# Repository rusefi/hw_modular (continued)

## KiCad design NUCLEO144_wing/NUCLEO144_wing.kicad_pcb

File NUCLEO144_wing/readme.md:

https://rusefi.com/forum/viewtopic.php?f=4&t=1522

Rev 0.1 send to fab 02/25/2019

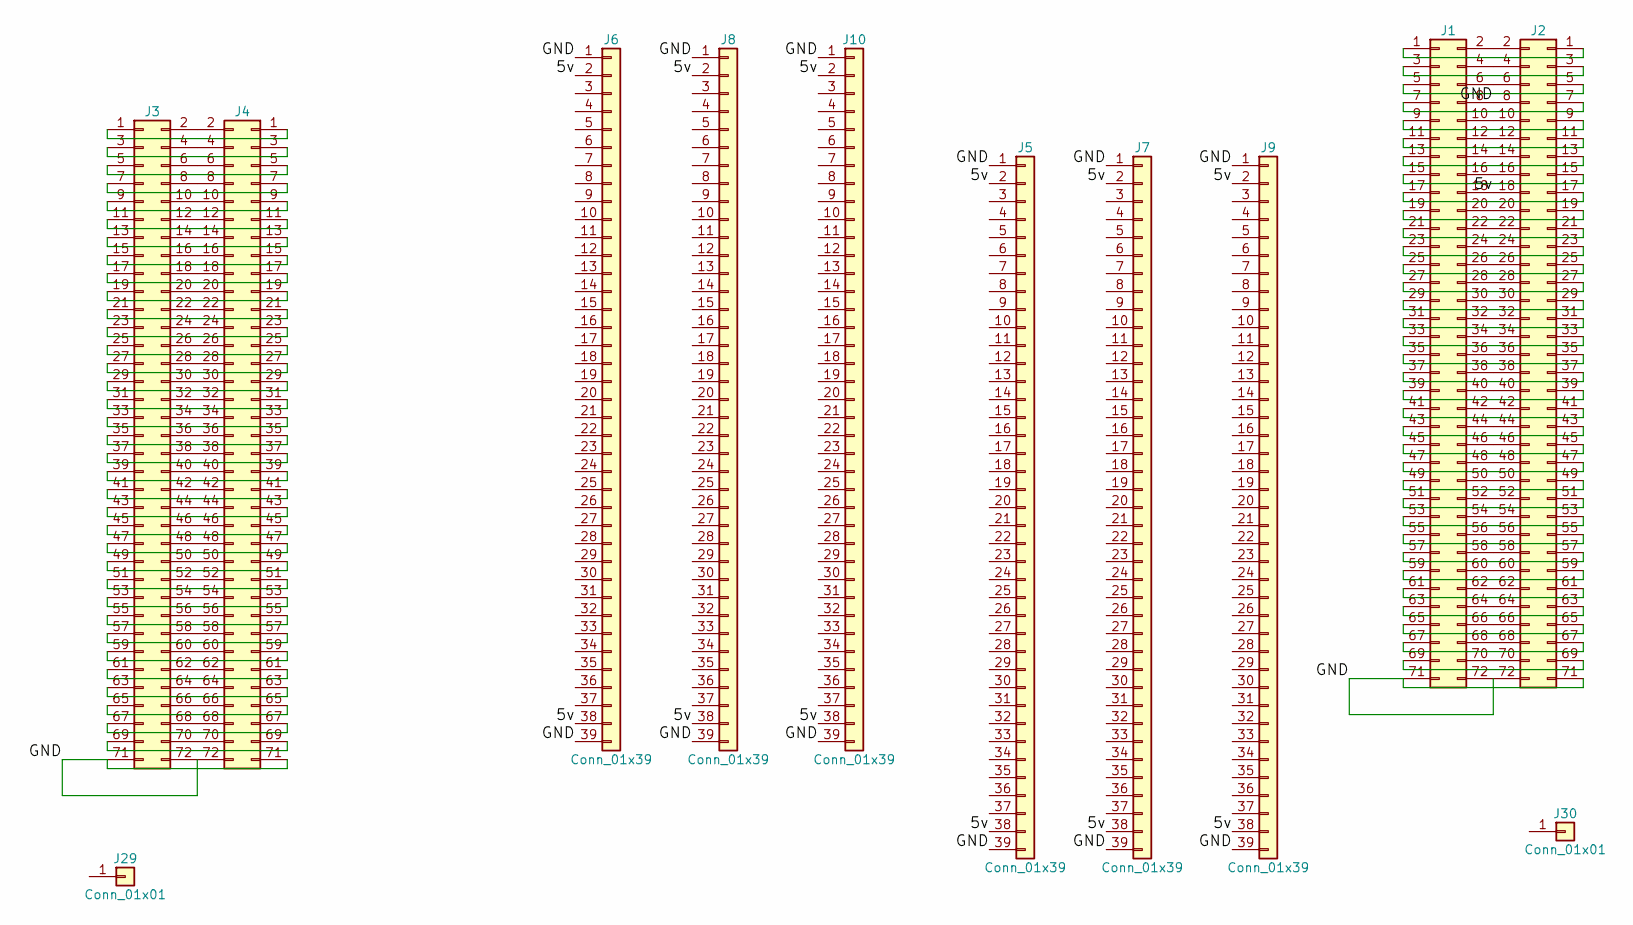
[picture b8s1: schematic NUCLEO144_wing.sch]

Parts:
J1, J2, J3, J4: Conn_02x36_Top_Bottom; Pin_Header_Straight_2x36_Pitch2.54mm
J5, J6, J7, J8, J9, J10: Conn_01x39; rusEfi_4x39_Pitch2.54mm
J29, J30: Conn_01x01; 1pin

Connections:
/5v: J1.18, J2.18, J5.2, J5.38, J6.2, J6.38, J7.2, J7.38, J8.2, J8.38, J9.2, J9.38, J10.2, J10.38
/GND: J1.8, J1.71, J1.72, J2.8, J2.71, J2.72, J3.71, J3.72, J4.71, J4.72, J5.1, J5.39, J6.1, J6.39, J7.1, J7.39, J8.1, J8.39, J9.1, J9.39, J10.1, J10.39
unnamed: J1.1, J2.1
unnamed: J1.2, J2.2
unnamed: J1.3, J2.3
unnamed: J1.4, J2.4
unnamed: J1.5, J2.5
unnamed: J1.6, J2.6
unnamed: J1.7, J2.7
unnamed: J1.9, J2.9
unnamed: J1.10, J2.10
unnamed: J1.11, J2.11
unnamed: J1.12, J2.12
unnamed: J1.13, J2.13
unnamed: J1.14, J2.14
unnamed: J1.15, J2.15
unnamed: J1.16, J2.16
unnamed: J1.17, J2.17
unnamed: J1.19, J2.19
unnamed: J1.20, J2.20
unnamed: J1.21, J2.21
unnamed: J1.22, J2.22
unnamed: J1.23, J2.23
unnamed: J1.24, J2.24
unnamed: J1.25, J2.25
unnamed: J1.26, J2.26
unnamed: J1.27, J2.27
unnamed: J1.28, J2.28
unnamed: J1.29, J2.29
unnamed: J1.30, J2.30
unnamed: J1.31, J2.31
unnamed: J1.32, J2.32
unnamed: J1.33, J2.33
unnamed: J1.34, J2.34
unnamed: J1.35, J2.35
unnamed: J1.36, J2.36
unnamed: J1.37, J2.37
unnamed: J1.38, J2.38
unnamed: J1.39, J2.39
unnamed: J1.40, J2.40
unnamed: J1.41, J2.41
unnamed: J1.42, J2.42
unnamed: J1.43, J2.43
unnamed: J1.44, J2.44
unnamed: J1.45, J2.45
unnamed: J1.46, J2.46
unnamed: J1.47, J2.47
unnamed: J1.48, J2.48
unnamed: J1.49, J2.49
unnamed: J1.50, J2.50
unnamed: J1.51, J2.51
unnamed: J1.52, J2.52
unnamed: J1.53, J2.53
unnamed: J1.54, J2.54
unnamed: J1.55, J2.55
unnamed: J1.56, J2.56
unnamed: J1.57, J2.57
unnamed: J1.58, J2.58
unnamed: J1.59, J2.59
unnamed: J1.60, J2.60
unnamed: J1.61, J2.61
unnamed: J1.62, J2.62
unnamed: J1.63, J2.63
unnamed: J1.64, J2.64
unnamed: J1.65, J2.65
unnamed: J1.66, J2.66
unnamed: J1.67, J2.67
unnamed: J1.68, J2.68
unnamed: J1.69, J2.69
unnamed: J1.70, J2.70
unnamed: J3.1, J4.1
unnamed: J3.2, J4.2
unnamed: J3.3, J4.3
unnamed: J3.4, J4.4
unnamed: J3.5, J4.5
unnamed: J3.6, J4.6
unnamed: J3.7, J4.7
unnamed: J3.8, J4.8
unnamed: J3.9, J4.9
unnamed: J3.10, J4.10
unnamed: J3.11, J4.11
unnamed: J3.12, J4.12
unnamed: J3.13, J4.13
unnamed: J3.14, J4.14
unnamed: J3.15, J4.15
unnamed: J3.16, J4.16
unnamed: J3.17, J4.17
unnamed: J3.18, J4.18
unnamed: J3.19, J4.19
unnamed: J3.20, J4.20
unnamed: J3.21, J4.21
unnamed: J3.22, J4.22
unnamed: J3.23, J4.23
unnamed: J3.24, J4.24
unnamed: J3.25, J4.25
unnamed: J3.26, J4.26
unnamed: J3.27, J4.27
unnamed: J3.28, J4.28
unnamed: J3.29, J4.29
unnamed: J3.30, J4.30
unnamed: J3.31, J4.31
unnamed: J3.32, J4.32
unnamed: J3.33, J4.33
unnamed: J3.34, J4.34
unnamed: J3.35, J4.35
unnamed: J3.36, J4.36
unnamed: J3.37, J4.37
unnamed: J3.38, J4.38
unnamed: J3.39, J4.39
unnamed: J3.40, J4.40
unnamed: J3.41, J4.41
unnamed: J3.42, J4.42
unnamed: J3.43, J4.43
unnamed: J3.44, J4.44
unnamed: J3.45, J4.45
unnamed: J3.46, J4.46
unnamed: J3.47, J4.47
unnamed: J3.48, J4.48
unnamed: J3.49, J4.49
unnamed: J3.50, J4.50
unnamed: J3.51, J4.51
unnamed: J3.52, J4.52
unnamed: J3.53, J4.53
unnamed: J3.54, J4.54
unnamed: J3.55, J4.55
unnamed: J3.56, J4.56
unnamed: J3.57, J4.57
unnamed: J3.58, J4.58
unnamed: J3.59, J4.59
unnamed: J3.60, J4.60
unnamed: J3.61, J4.61
unnamed: J3.62, J4.62
unnamed: J3.63, J4.63
unnamed: J3.64, J4.64
unnamed: J3.65, J4.65
unnamed: J3.66, J4.66
unnamed: J3.67, J4.67
unnamed: J3.68, J4.68
unnamed: J3.69, J4.69
unnamed: J3.70, J4.70

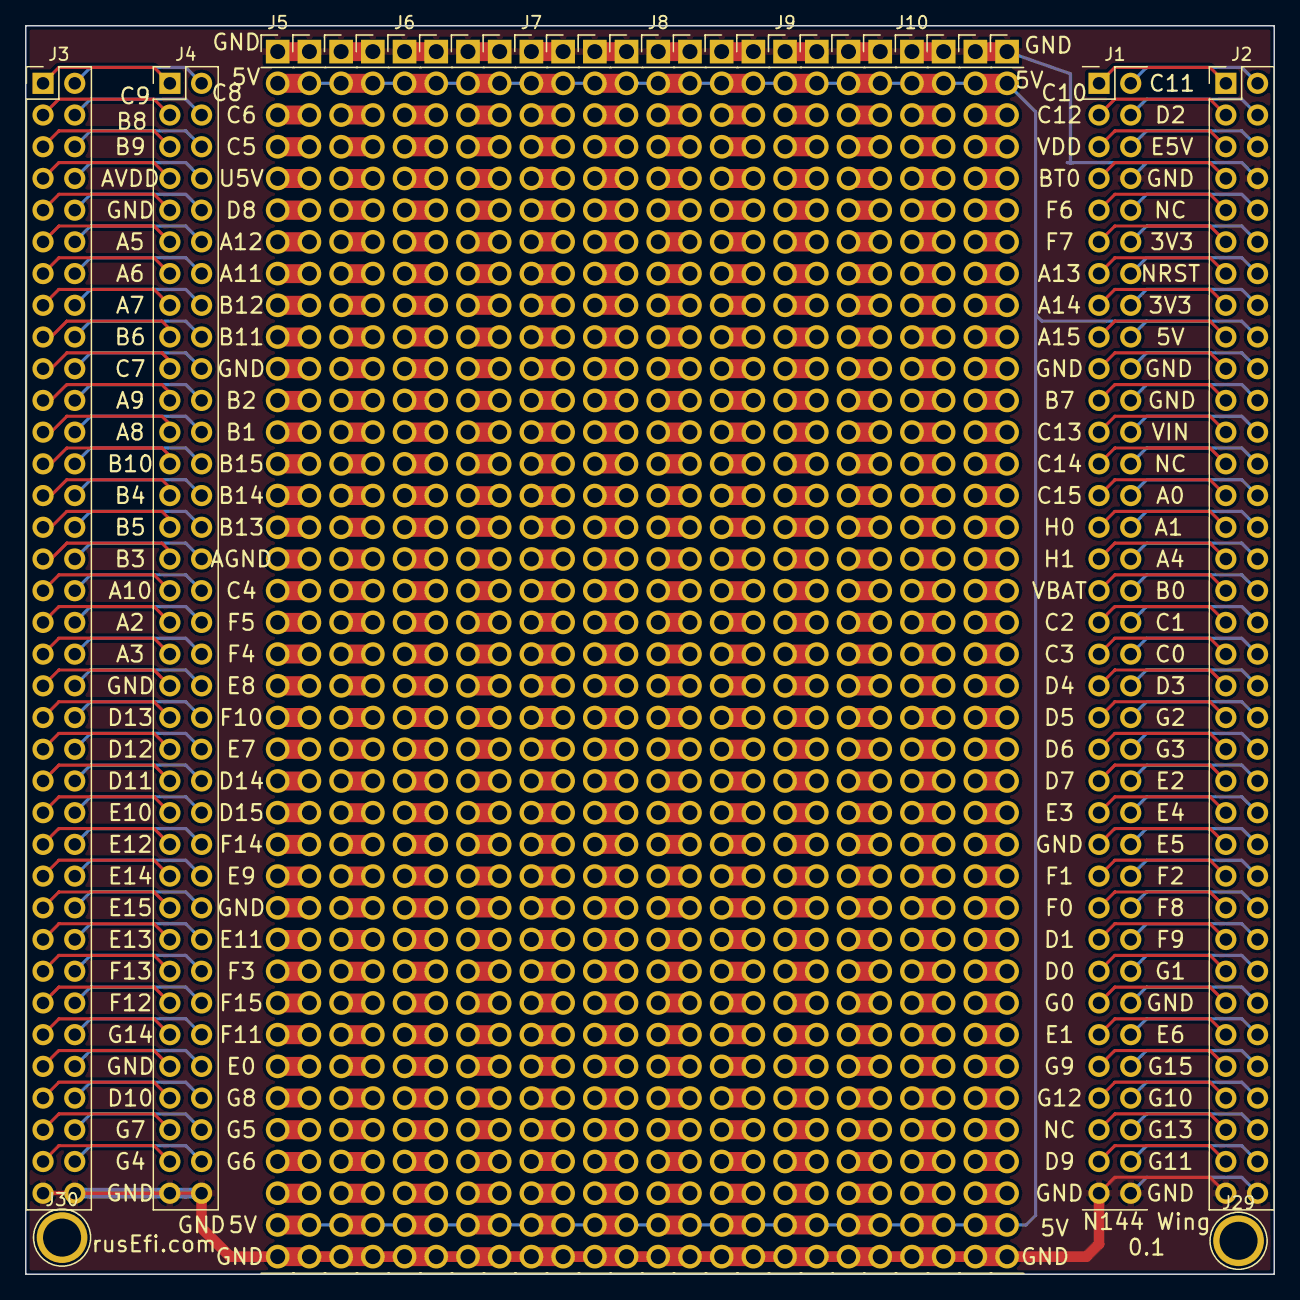
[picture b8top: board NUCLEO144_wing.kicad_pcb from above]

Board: 2 copper layers, 100.0 x 100.0 mm, 12 parts (0 on the bottom side), 140 nets.

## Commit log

2019-02-25 module dependecy
2019-02-25 initial version
2019-02-26 to fab shop!
2019-02-26 sorry for party
2019-02-26 docs
2019-03-04 need help with tle7209
2019-03-09 moving from https://github.com/rusefi/rusefi/tree/master/hardware/TLE8110ED_breakout_board
2019-03-09 wishes for 0.2
2019-03-12 wing
2019-03-12 gerbers
2019-03-12 progress
2019-03-12 now with drill file
2019-03-13 .gitignore
2019-04-26 gerbers 0.1
2019-04-27 links
2019-04-27 sync
2019-04-27 rename
2019-04-27 2 layer release
2019-04-30 silkscreen
2019-05-05 another module!
2019-05-25 pics
2019-05-25 Corrected diode symbols and cleaned sym-lib-table
2019-05-26 wrong diode symbol
2019-05-27 components progress
2019-05-27 cleaned up
2019-05-27 manual sync with 960
2019-05-27 who loves git?
2019-05-27 updated bom
2019-05-27 Full cleanup of analog input module
2019-05-27 new try. With IBOM
2019-05-27 new try, with IBOM
2019-05-27 manual sync
2019-05-27 manually produced BOMs
2019-05-27 .net help with iBom
2019-05-27 netlist
2019-06-07 V 0.2
2019-06-08 V 0.2 (#19)
2019-08-03 test board 48
2019-12-22 size
2020-01-08 Small update
2020-01-08 Updated with LSLC Pn
2020-01-08 Pcb Update
2020-01-08 larger cap
2020-01-08 Corrected schematic with LSLC Parts numbers (#25)
    * Small update
    * Updated with LSLC Pn
    * pdf
    * Pcb Update
    * Gerbers
    * larger cap
2020-01-08 version
2020-01-08 version (#27)
2020-01-08 V 0.3
2020-01-08 V 0.3 (#30)
    * gerbers
    * version
    * V 0.3
2020-01-10 positions & better names
2020-01-11 reducing confusion
2020-01-22 update submodule
2020-01-24 gitignore
2020-01-24 low side module
2020-01-24 name sheets
2020-01-24 update submodule (#31)
2020-02-10 add 7th pair
2020-02-10 tweak gitignore
2020-02-11 14ch low side driver (#32)
    * update submodule
    * gitignore
    * low side module
    * name sheets
    * add 7th pair
    * tweak gitignore
2020-02-15 Wideband Module
2020-02-15 Wideband Module (#33)
2020-02-15 Updated properties in schematic closer to allowing BOM export.
2020-02-15 Removed DRC issues.
2020-02-16 Generated gerbers and BOM for MFG.
2020-02-27 getting ready for assembly
2020-02-27 fresh PDF
2020-03-10 more available part number
2020-03-15 BOM progress
2020-03-22 draft
2020-03-22 pinout
2020-03-22 added files
2020-03-23 R0.1
2020-03-28 ibom reference
2020-04-05 corrections
2020-04-05 C4 value notes 100uf on schematic and PCB silk R4 & R5 now note 2.2K generated schematic PDF as 0.3
2020-04-08 fabrication progress
2020-04-09 test
2020-04-10 Added notes to schematic
2020-05-03 Connected pin 5 to 5V
2020-05-03 Added symbol file
2020-05-11 ibom progress
2020-05-17 R0.1.1 released added 5V connection to CJ125
2021-11-08 Update Manhattan_standard.md
    https://forum.kicad.info/t/warning-avoid-all-links-to-kicad-pcb-org-use-kicad-org/31521
